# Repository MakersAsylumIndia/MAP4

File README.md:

# MAP4
a really easy, "learn to solder" Maker's Asylum Badge
consisting of two LED's and a battery

**Maker's Asylum Project #7**

***FEATURES***

1. Two LED's with series current limit resistors
2. One CR2032 Coin Battery
3. Use Red, Green, Blue or White LEDs
4. Use Blinking LEDs
5. Replace Resistor with LDR to have light controlled brightness

***LEARN***

1. How to Solder
2. Resistor Color Code
3. Use of Multimeter to check LED, Resistor and Battery

rev1 renders

License
-------
[CERN Open Hardware Licence v1.2 ]

[CERN Open Hardware Licence v1.2 ]:http://www.ohwr.org/attachments/2388/cern_ohl_v_1_2.txt

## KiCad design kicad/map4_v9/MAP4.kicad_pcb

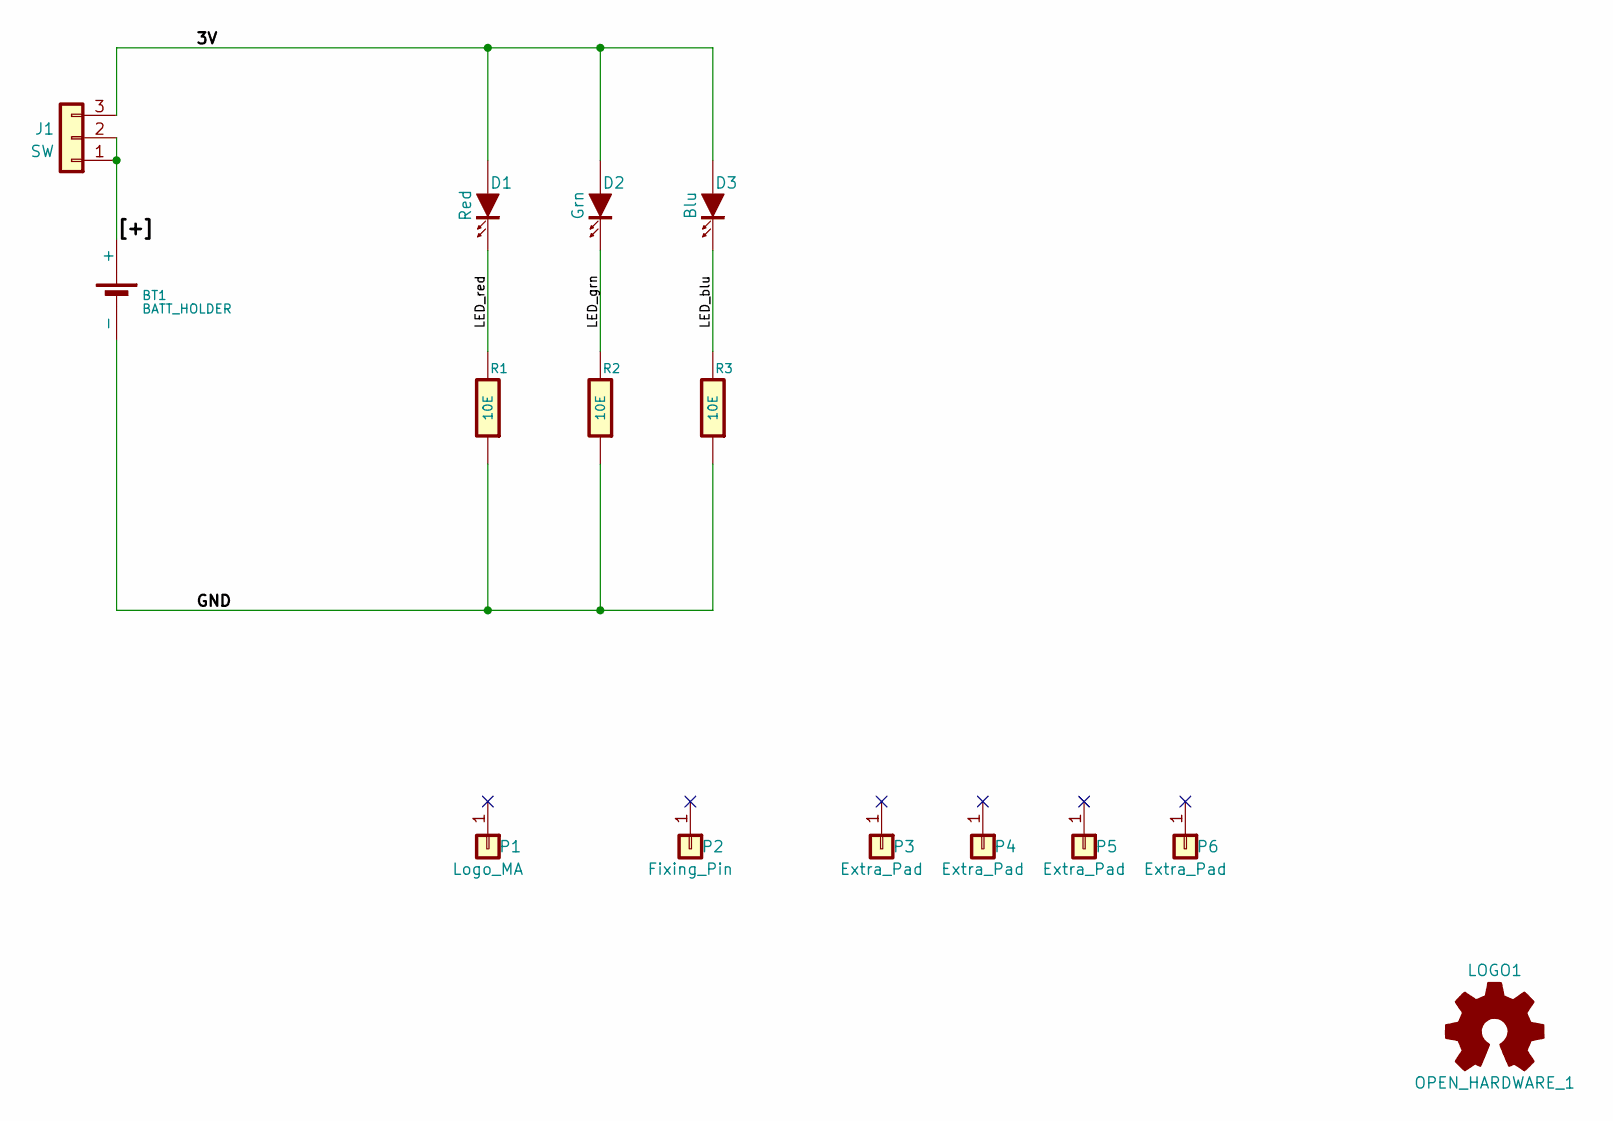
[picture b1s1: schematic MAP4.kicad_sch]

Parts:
BT1: BATT_HOLDER; cr2032_02
D1: Red; LED-5MM
D2: Grn; LED-5MM
D3: Blu; LED-5MM_INV
J1: SW; PinHeader_1x03_P2.54mm_Vertical
LOGO1: OPEN_HARDWARE_1; Logo_silk_OSHW_6x6mm
P1: Logo_MA; MA_LOGO4
P2: Fixing_Pin; MTG_3mmx1mm2
P3, P4, P5, P6: Extra_Pad; MTG_0mm8
R1, R2, R3: 10E; r_0805

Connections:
/3V: D1.1 (A), D2.1 (A), D3.1 (A), J1.3
/GND: BT1.2 (-), R1.1, R2.1, R3.1
/LED_blu: D3.2 (K), R3.2
/LED_grn: D2.2 (K), R2.2
/LED_red: D1.2 (K), R1.2
/[+]: BT1.1 (+), J1.1, J1.2

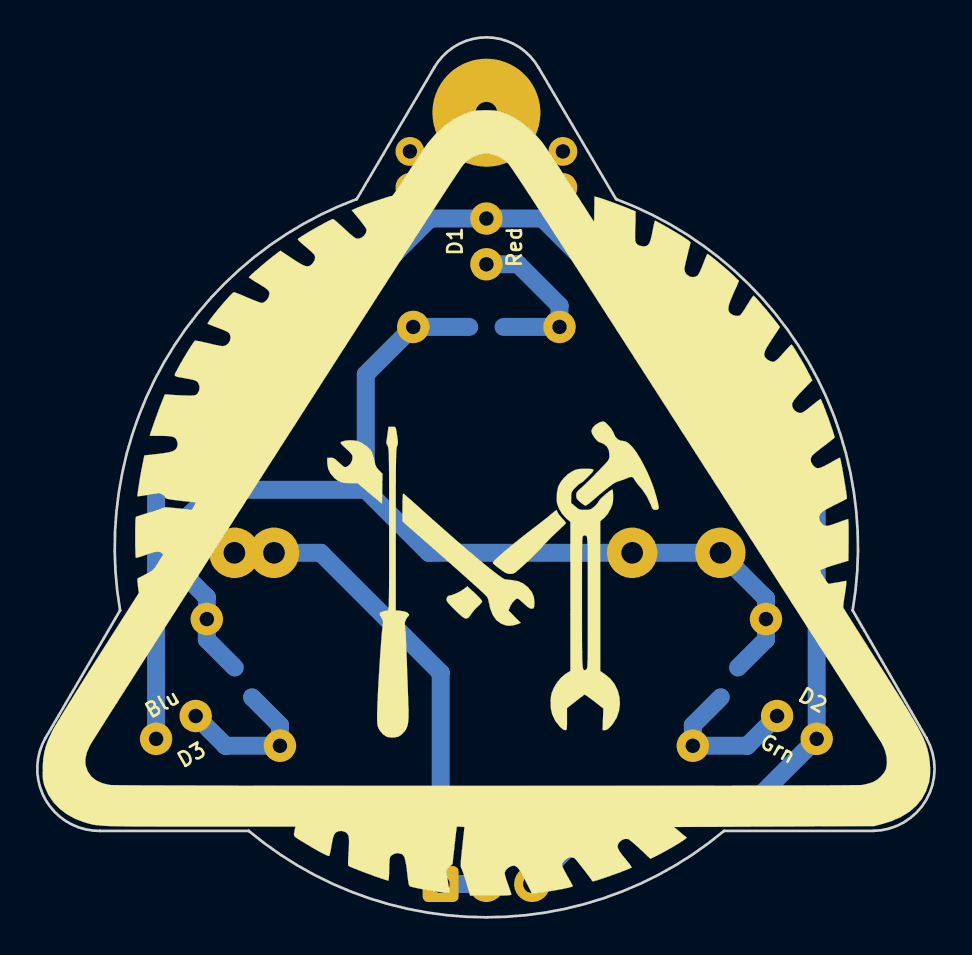
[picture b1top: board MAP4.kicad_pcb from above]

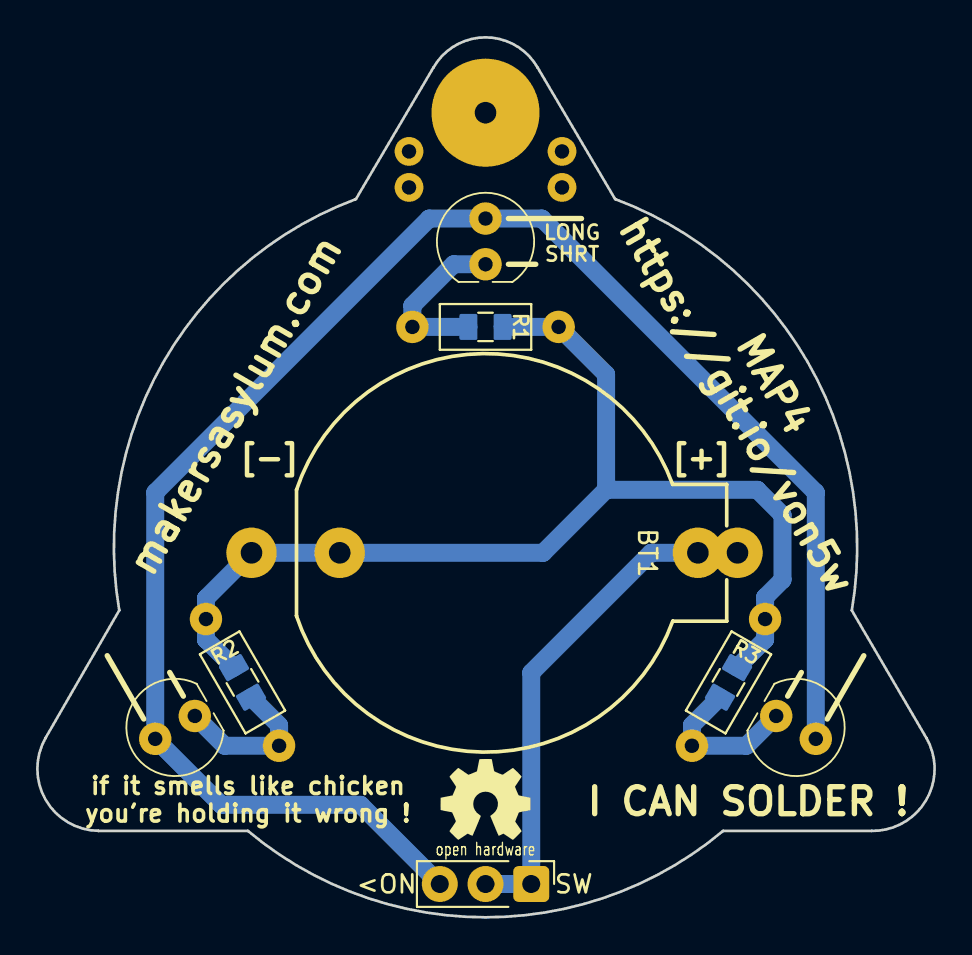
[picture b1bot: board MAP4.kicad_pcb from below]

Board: 2 copper layers, 49.8 x 48.9 mm, 15 parts (6 on the bottom side), 6 nets.

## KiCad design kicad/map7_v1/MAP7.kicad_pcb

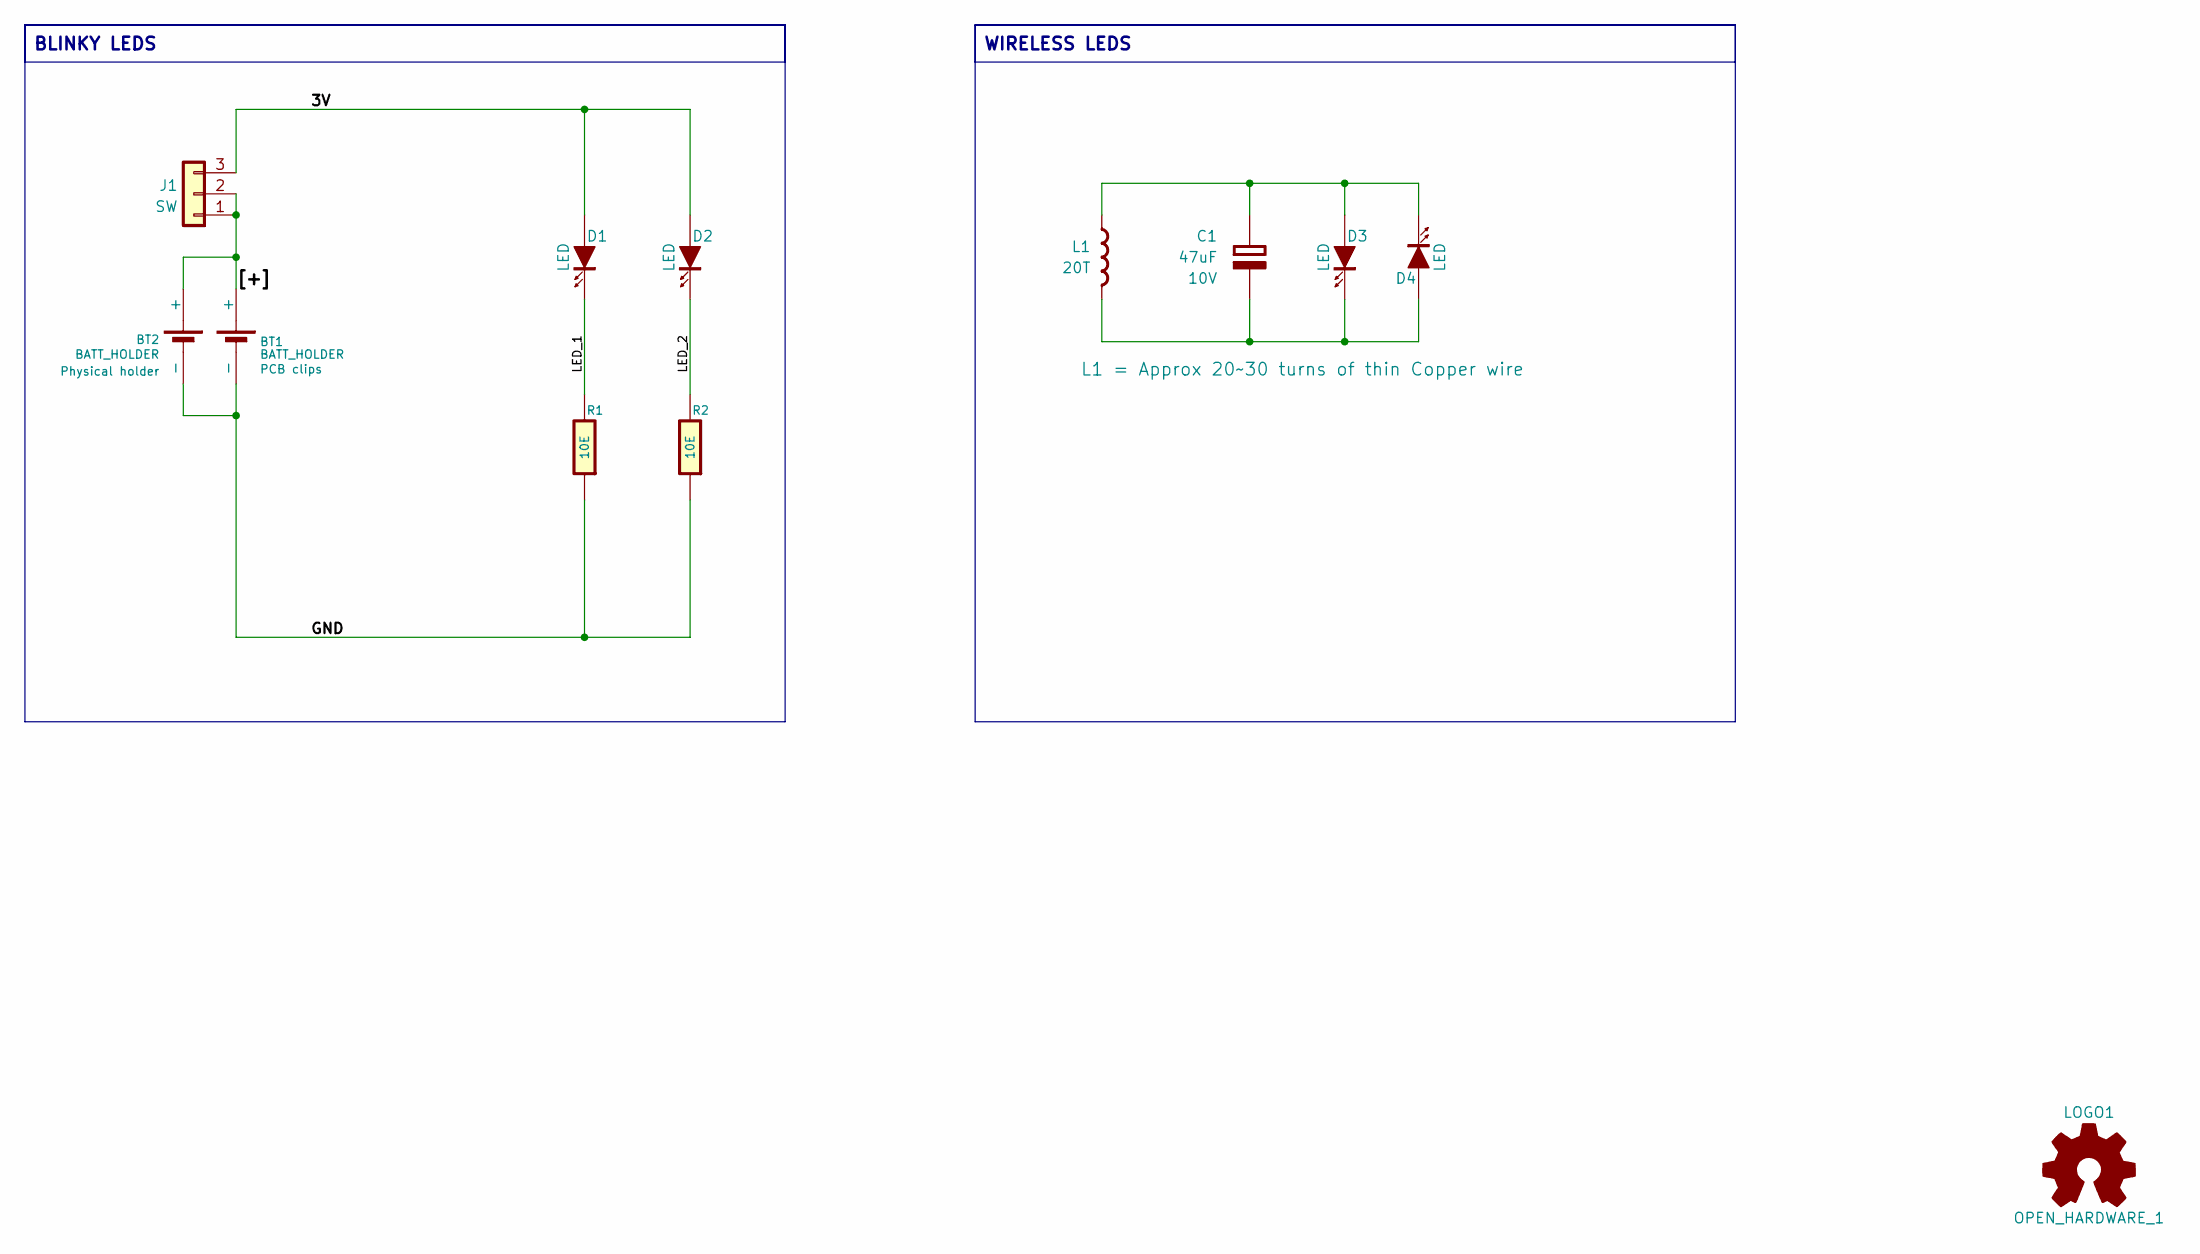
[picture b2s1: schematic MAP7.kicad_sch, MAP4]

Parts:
BT1: BATT_HOLDER; pick-battery-jsc
BT2: BATT_HOLDER; cr2032_02
C1: 47uF; CP_Radial_D5.0mm_P2.50mm; Rating 10V
D1, D3: LED; LED-5MM-horiz_left
D2, D4: LED; LED-5MM-horiz_right
J1: SW; PinHeader_1x03_P2.54mm_Vertical
L1: 20T; PinHeader_1x02_P2.54mm_Vertical; Rating A
LOGO1: OPEN_HARDWARE_1; Logo_silk_OSHW_6x6mm
R1, R2: 10E; r_0805

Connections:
/3V: D1.1 (A), D2.1 (A), J1.3
/GND: BT1.2 (-), BT2.2 (-), R1.1, R2.1
/LED_1: D1.2 (K), R1.2
/LED_2: D2.2 (K), R2.2
/[+]: BT1.1 (+), BT2.1 (+), J1.1, J1.2
unnamed: C1.1 (+), D3.1 (A), D4.2 (K), L1.1 (+)
unnamed: C1.2 (-), D3.2 (K), D4.1 (A), L1.2 (-)

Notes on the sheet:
BLINKY LEDS
WIRELESS LEDS

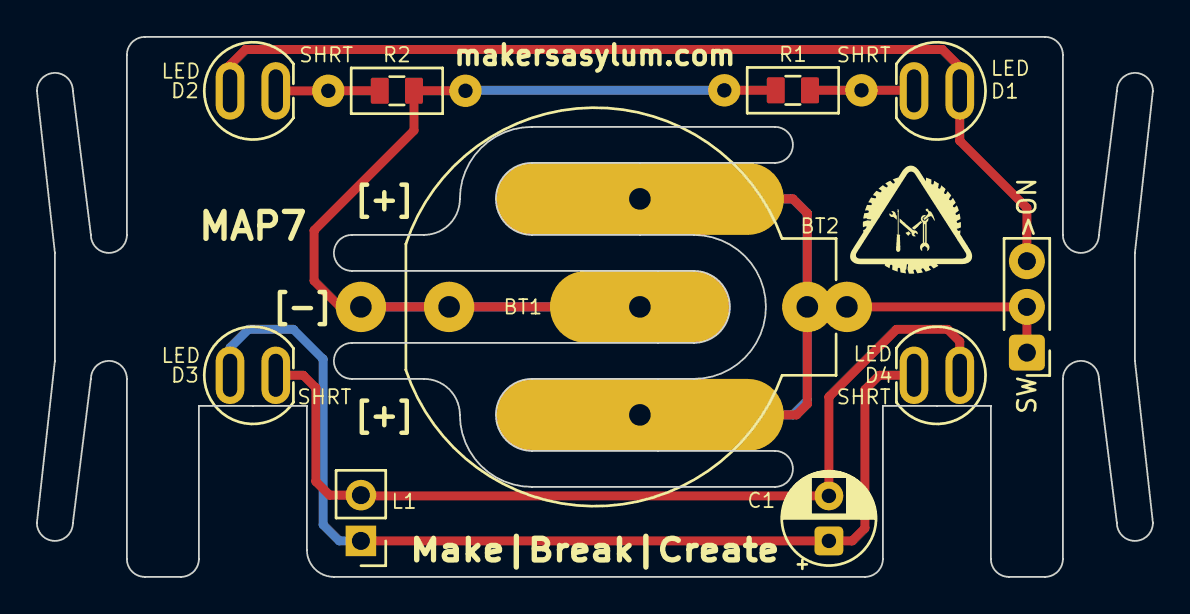
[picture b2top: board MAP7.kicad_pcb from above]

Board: 2 copper layers, 62.0 x 30.0 mm, 12 parts (1 on the bottom side), 7 nets.

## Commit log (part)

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2016-05-24 MAP4 work in progress
2016-05-24 work in progress
2016-05-25 MAP4 complete. Boards ordered out
2016-05-27 MAP4 revised Gerbers to clear PCBpower issue
2016-05-30 MAP4 added link to Discuss forum
2016-06-06 added some pictures of the PCB
2016-06-12 Battery holder footprint correction. New Legend
2016-06-12 added fresh render images
2016-07-28 rev4 of MAP4 with battery holderfootprint fixed and minor track changes
2017-05-16 minor edits to bottom silk layer for PCBpower ETOK mark issue
2017-05-19 added invert_mask folder for Yellow Mask/Black Legend
2017-06-13 spinner models added
2017-06-14 spinner, bearing size 6006
2017-06-16 spinner, bearing size 6006, STL
2017-07-09 new 608 spinner design for three MAP4 badges
2017-07-10 map4 spinner minor mod
2022-05-27 added some description to readme.md
2025-10-29 Blinky Badge v9 with switch and other enhancements
2026-05-04 cleanup
